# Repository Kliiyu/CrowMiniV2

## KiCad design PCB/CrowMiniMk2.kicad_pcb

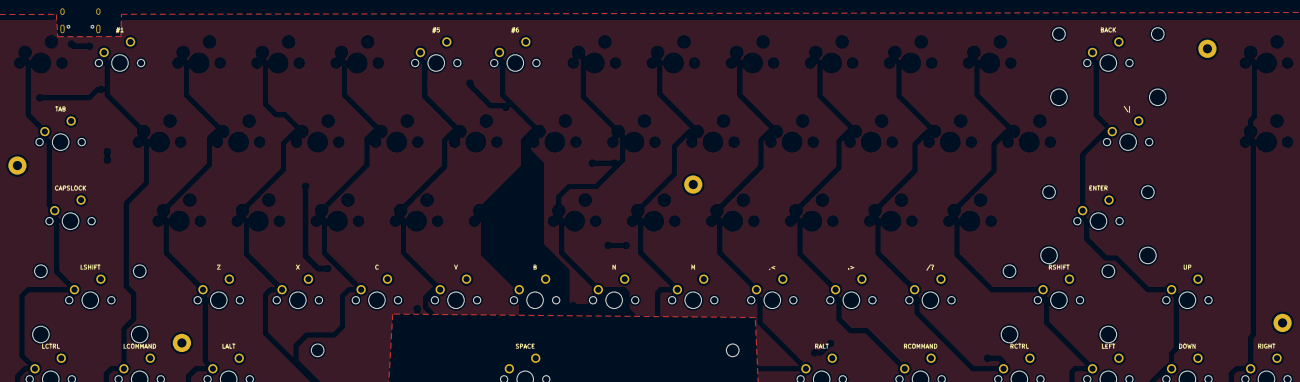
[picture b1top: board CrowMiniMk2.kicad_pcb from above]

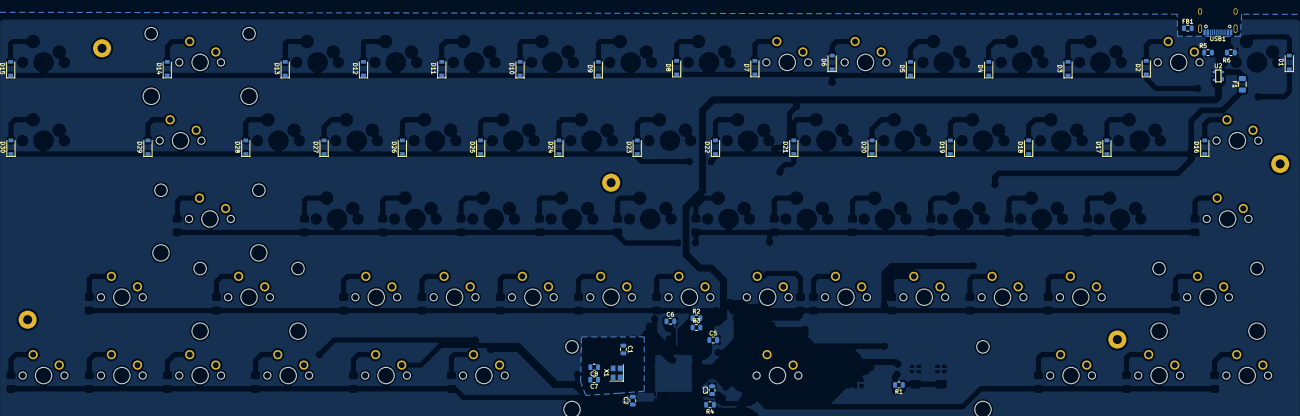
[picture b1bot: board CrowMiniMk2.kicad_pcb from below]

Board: 2 copper layers, 85 parts (48 on the bottom side), 28 nets, no tracks yet.

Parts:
C1, C2, C3: 0.1u; C_0805_2012Metric
C5: 10u; C_0805_2012Metric
C6: 1u; C_0805_2012Metric
C7, C8: 22p; C_0805_2012Metric
D1, D2, D3, D4, D5, D6, D7, D8, D9, D10, D11, D12, D13, D14, D15, D16, D17, D18, D19, D20, D21, D22, D23, D24, D25, D26, D27, D28, D29, D30: D; D_SOD-123
F1: 500; Fuse_1206_3216Metric
FB1: 60@100Mhz; L_0805_2012Metric
H1, H2, H3, H4, H5: MountingHole; MountingHole_2.2mm_M2_Pad
K2: #1; MXOnly-1U-NoLED
K6: #5; MXOnly-1U-NoLED
K7: #6; MXOnly-1U-NoLED
K14: BACK; MXOnly-2U-NoLED
K16: TAB; MXOnly-1.5U-NoLED
K29: \|; MXOnly-1.5U-NoLED
K31: CAPSLOCK; MXOnly-1.75U-NoLED
K42: '; MXOnly-1U-NoLED
K43: ENTER; MXOnly-2.25U-NoLED
K44: LSHIFT; MXOnly-2.25U-NoLED
K45: Z; MXOnly-1U-NoLED
K46: X; MXOnly-1U-NoLED
K47: C; MXOnly-1U-NoLED
K48: V; MXOnly-1U-NoLED
K49: B; MXOnly-1U-NoLED
K50: N; MXOnly-1U-NoLED
K51: M; MXOnly-1U-NoLED
K52: ,<; MXOnly-1U-NoLED
K53: .>; MXOnly-1U-NoLED
K54: /?; MXOnly-1U-NoLED
K55: RSHIFT; MXOnly-2.25U-NoLED
K56: UP; MXOnly-1U-NoLED
K57: LCTRL; MXOnly-1.25U-NoLED
K58: LCOMMAND; MXOnly-1U-NoLED
K59: LALT; MXOnly-1.25U-NoLED
K60: SPACE; MXOnly-6.25U-NoLED
K61: RALT; MXOnly-1.25U-NoLED
K62: RCOMMAND; MXOnly-1.25U-NoLED
K63: RCTRL; MXOnly-1.25U-NoLED
K64: LEFT; MXOnly-1U-NoLED
K65: DOWN; MXOnly-1U-NoLED
K66: RIGHT; MXOnly-1U-NoLED
R1, R4: 10k; R_0805_2012Metric
R2, R3: 22; R_0805_2012Metric
R5, R6: 5.1k; R_0805_2012Metric
U2: PRTR5V0U2X; SOT143B
USB1: HRO-TYPE-C-31-M-12
X1: XTAL; Crystal_SMD_3225-4Pin_3.2x2.5mm

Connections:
+5V: C1.1, C2.1, C3.1, C5.1, F1.1, R1.2
COL0: K16.1, K31.1, K44.1, K57.1
COL1: K2.1, K58.1
COL2: K45.1, K59.1
COL5: K6.1, K48.1
COL6: K7.1, K49.1, K60.1
COL9: K52.1, K61.1
COL10: K53.1, K62.1
COL11: K54.1, K63.1
COL12: K55.1, K64.1
COL13: K14.1, K29.1, K43.1, K56.1, K65.1
D+: R2.2, U2.4, USB1.6, USB1.8
D-: R3.2, U2.1, USB1.5, USB1.7
Earth: FB1.2, USB1.13
GND: C1.2, C2.2, C3.2, C5.2, C6.2, C7.2, C8.2, FB1.1, R4.1, R5.1, R6.1, U2.3, USB1.1, USB1.12, X1.2, X1.4
unnamed: D2.2, K2.2
unnamed: D6.2, K6.2
unnamed: D7.2, K7.2
unnamed: D14.2, K14.2
unnamed: D16.2, K16.2
unnamed: D29.2, K29.2
unnamed: R5.2, USB1.10
unnamed: R6.2, USB1.4
ROW0: D1.1, D2.1, D3.1, D4.1, D5.1, D6.1, D7.1, D8.1, D9.1, D10.1, D11.1, D12.1, D13.1, D14.1, D15.1
ROW1: D16.1, D17.1, D18.1, D19.1, D20.1, D21.1, D22.1, D23.1, D24.1, D25.1, D26.1, D27.1, D28.1, D29.1, D30.1
VCC: F1.2, U2.2, USB1.2, USB1.11
XTAL1: C7.1, X1.1
XTAL2: C8.1, X1.3

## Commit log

2021-09-26 FSetup
2021-09-26 Add submodules
2021-09-26 Add footprint libraries
2021-09-26 Matrix And MCU
2021-09-26 Sch Finish
2021-09-26 Pre routing
2021-09-26 Some routing done
2021-09-27 Routing 99%
2021-09-27 Pre Logo add
2021-09-27 Save2
2021-09-27 PreManufacturingAndLogo Save
2021-09-28 Case and Logo Start
2021-09-28 Case progress 1
2021-09-28 PCB Manufacturing
2021-10-01 Save
2021-10-18 Save1.2.2
2021-10-18 Save1.2.3
2021-10-18 Save1.2.4
2021-10-21 Remove old case
2022-02-15 Protection
2022-02-15 Firmware

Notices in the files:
PCB/CrowMiniMk2.kicad_pcb:
V1.2.2 - © Adrian H. Evjeberg 2021
